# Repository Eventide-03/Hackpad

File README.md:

# Hackpad
My first custom PCB made for KiCAD practice and learning of the basics.

<https://cad.onshape.com/documents/e786a7be914fb18be4e0ebf1/w/963e0963644aadd8b2596800/e/8d5c500a34f69e400152063b?renderMode=0&uiState=6924ddcc17631571da62c134>

# BOM
- My PCB (duhh)
- Seeed XIAO RP2040 DIP
- 2 SK6812 MINI-E LEDs
- M3x16mm screws
- M3x5mx4mm heatset inserts

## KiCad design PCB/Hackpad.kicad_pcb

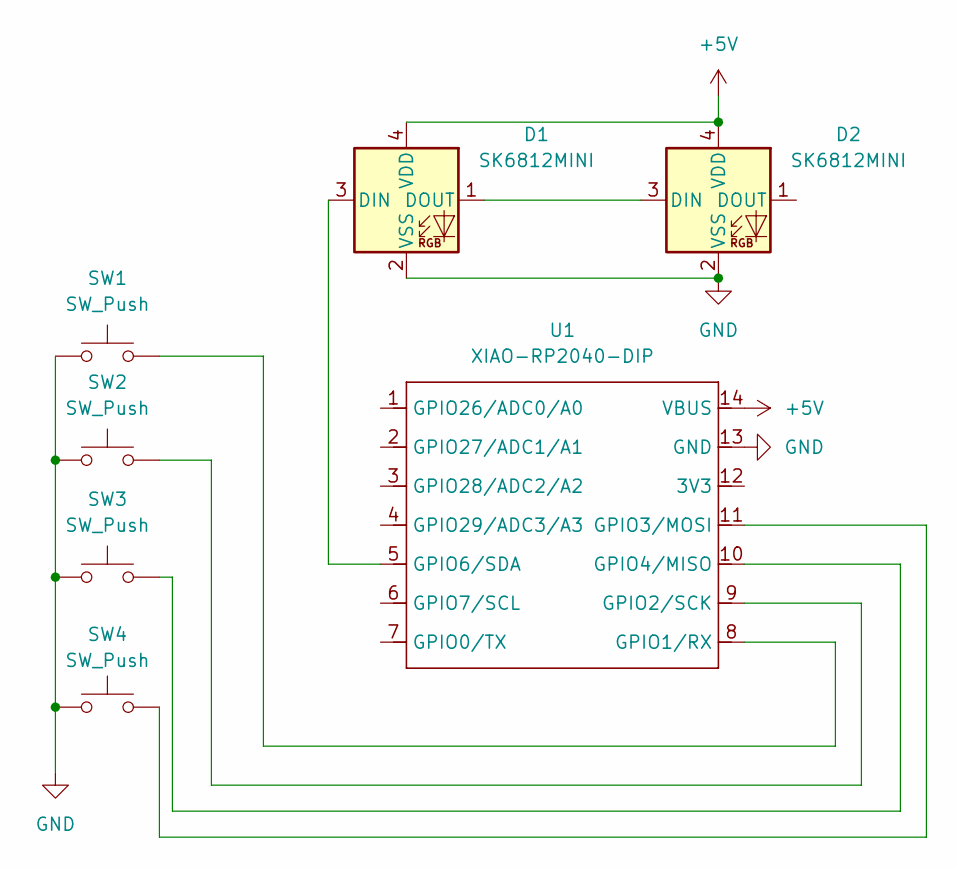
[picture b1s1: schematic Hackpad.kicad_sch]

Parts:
D1, D2: SK6812MINI; LED_SK6812MINI_PLCC4_3.5x3.5mm_P1.75mm
SW1, SW2, SW3, SW4: SW_Push; SW_Cherry_MX_1.00u_PCB
U1: XIAO-RP2040-DIP

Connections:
+5V: D1.4 (VDD), D2.4 (VDD), U1.14 (VBUS)
GND: D1.2 (VSS), D2.2 (VSS), SW1.2, SW2.1, SW3.1, SW4.1, U1.13 (GND)
unnamed: D1.3 (DIN), U1.5 (GPIO6/SDA)
unnamed: D1.1 (DOUT), D2.3 (DIN)
unnamed: SW1.1, U1.8 (GPIO1/RX)
unnamed: SW2.2, U1.9 (GPIO2/SCK)
unnamed: SW4.2, U1.11 (GPIO3/MOSI)
unnamed: SW3.2, U1.10 (GPIO4/MISO)

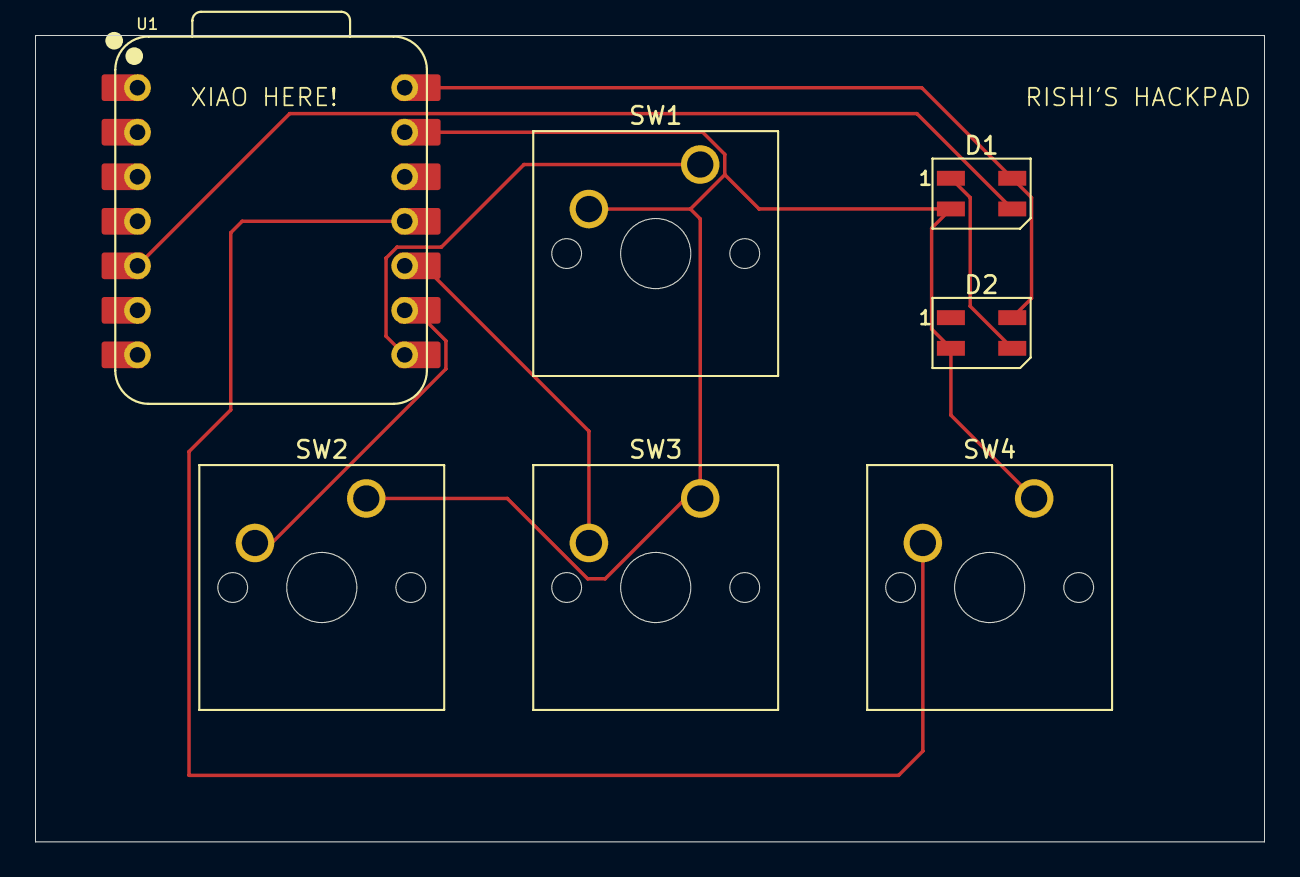
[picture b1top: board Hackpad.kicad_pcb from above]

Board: 2 copper layers, 70.1 x 46.0 mm, 7 parts (0 on the bottom side), 8 nets.

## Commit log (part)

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2025-11-24 Initial plan
2025-11-24 Create empty hardware folder
2025-11-24 Everything.
2025-11-24 Images and BOM information
    Added images and BOM details for the Hackpad PCB.
2025-11-24 fixed kicad files
2025-11-24 added gerber files and zip
2025-11-24 Update README with project link and images
    Added images and a link to the Hackpad project.
2025-11-25 updated gerber files
